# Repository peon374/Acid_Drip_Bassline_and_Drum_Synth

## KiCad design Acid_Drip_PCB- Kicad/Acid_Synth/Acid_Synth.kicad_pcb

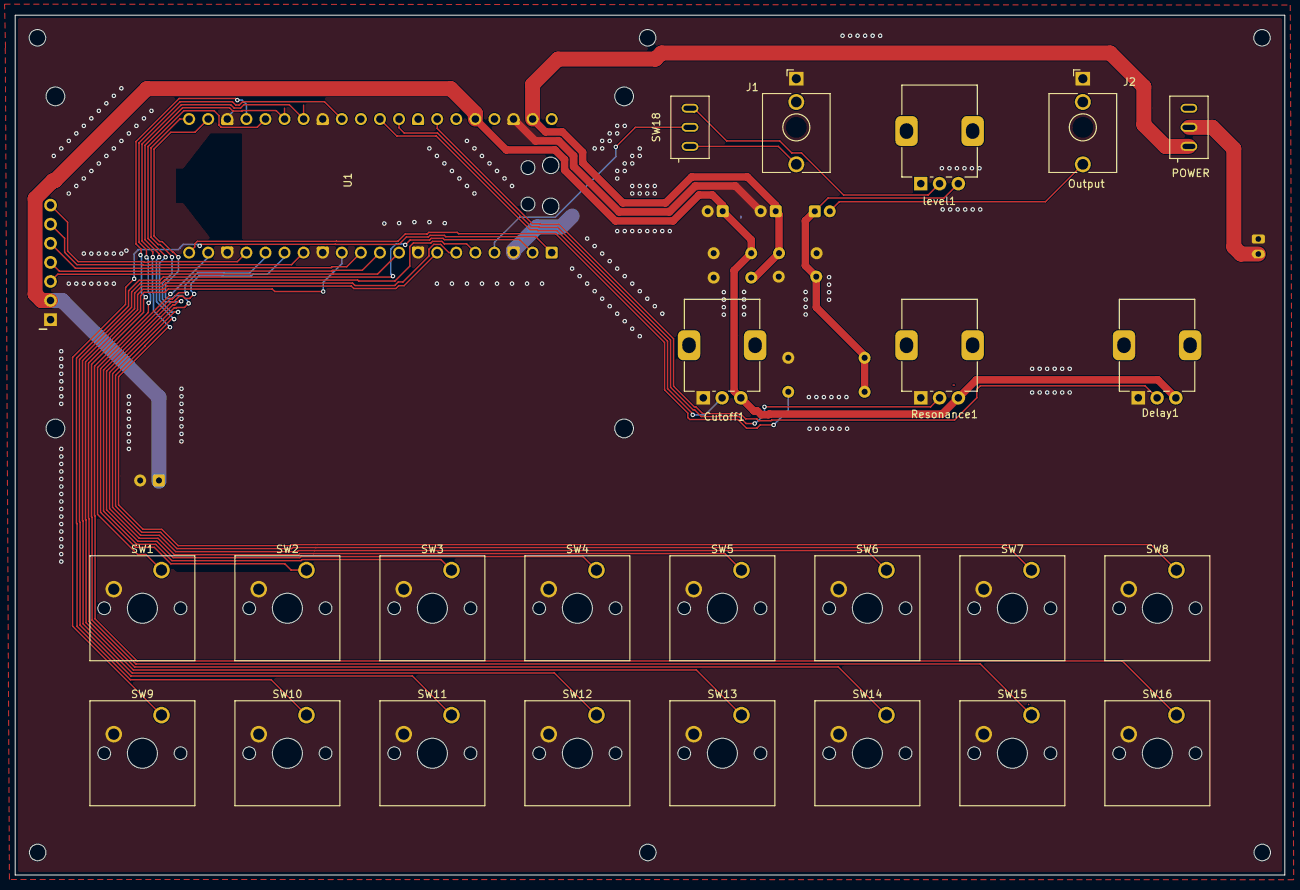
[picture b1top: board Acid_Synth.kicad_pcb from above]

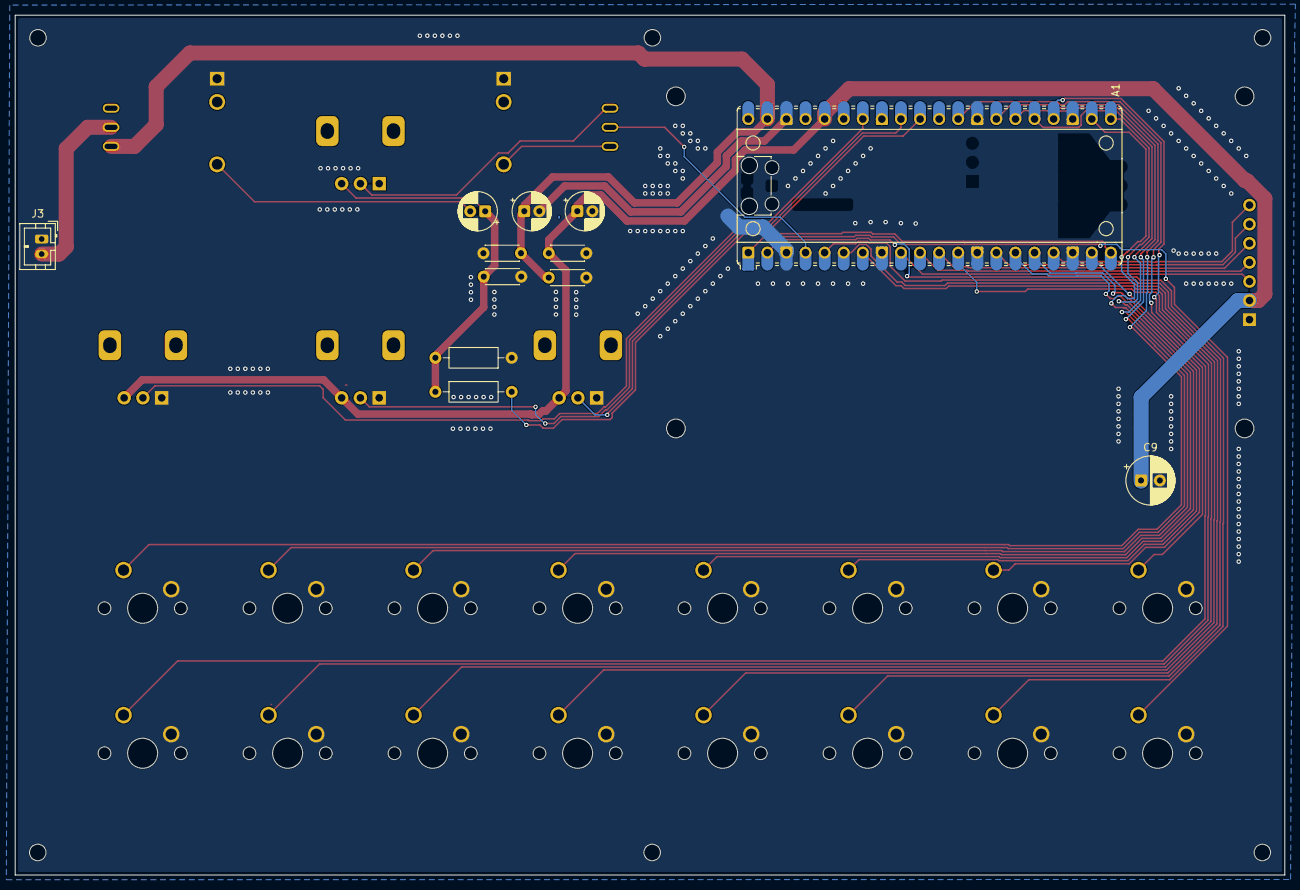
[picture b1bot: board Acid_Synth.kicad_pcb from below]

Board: 2 copper layers, 169.0 x 114.4 mm, 37 parts (12 on the bottom side), 33 nets.

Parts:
A1: RaspberryPi_Pico; RaspberryPi_Pico_Common
C1, C2, C4: 100nf; C_Disc_D4.3mm_W1.9mm_P5.00mm
C3, C5, C6: 100uf; CP_Radial_D5.0mm_P2.00mm
C7: 10nf; C_Disc_D4.3mm_W1.9mm_P5.00mm
C9: 1000uf; CP_Radial_D6.3mm_P2.50mm
Cutoff1: 10K; Potentiometer_Alps_RK09K_Single_Vertical
Delay1: 10K; Potentiometer_Alps_RK09K_Single_Vertical
J1: Sync_In; Jack_3.5mm_QingPu_WQP-PJ398SM_Vertical_CircularHoles
J2: Output; Jack_3.5mm_QingPu_WQP-PJ398SM_Vertical_CircularHoles
J3: Conn_01x02_Socket; JST_PH_B2B-PH-K_1x02_P2.00mm_Vertical
R1: 3.3K; R_Axial_DIN0207_L6.3mm_D2.5mm_P10.16mm_Horizontal
R3: 10K; R_Axial_DIN0207_L6.3mm_D2.5mm_P10.16mm_Horizontal
Resonance1: 10K; Potentiometer_Alps_RK09K_Single_Vertical
SW1, SW2, SW3, SW4, SW5, SW6, SW7, SW8, SW9, SW10, SW11, SW12, SW13, SW14, SW15, SW16: SW_Cherry_MX_1.00u_PCB
SW17: POWER; SW_SPDT_Toggle_QuarterInch_Bushing
SW18: SW_SPDT; SW_SPDT_Toggle_QuarterInch_Bushing
U1: TFT_2.8in_ILI9341
level1: 50K; Potentiometer_Alps_RK09K_Single_Vertical

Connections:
+3.3V: A1.36 (3V3), C2.1, C3.1, C9.1, Cutoff1.3, Delay1.3, Resonance1.3, U1.2 (VCC)
+5V: A1.39 (VSYS), C1.1, C4.1, C5.1, SW17.1 (A)
+BATT: J3.2, SW17.2 (B)
CS: A1.17 (GPIO13), U1.7 (CS)
Cutoff: A1.31 (GPIO26_ADC0), Cutoff1.2
DC: A1.14 (GPIO10), U1.6 (DC)
Decay: A1.34 (GPIO28_ADC2), Delay1.2
GND: A1.3 (GND), A1.8 (GND), A1.13 (GND), A1.18 (GND), A1.23 (GND), A1.28 (GND), A1.38 (GND), C1.2, C2.2, C3.2, C4.2, C5.2, C7.1, C9.2, Cutoff1.1, Delay1.1, J1.S, J2.S, J3.1, R1.1, Resonance1.1, SW1.2, SW2.2, SW3.2, SW4.2, SW5.2, SW6.2, SW7.2, SW8.2, SW9.2, SW10.2, SW11.2, SW12.2, SW13.2, SW14.2, SW15.2, SW16.2, U1.1 (GND)
NODE: C6.1, C7.2, R1.2, R3.1, level1.3
unnamed: C6.2, J2.T
unnamed: J1.T, SW18.1 (A)
OUTPUT: A1.20 (GPIO15), R3.2
RST: A1.11 (GPIO8), U1.5 (RST)
Resonance: A1.32 (GPIO27_ADC1), Resonance1.2
SCL: A1.9 (GPIO6), U1.3 (SCL)
SDA: A1.10 (GPIO7), U1.4 (SDA)
SW1: A1.19 (GPIO14), SW1.1
SW2: A1.16 (GPIO12), SW2.1
SW3: A1.15 (GPIO11), SW3.1
SW4: A1.21 (GPIO16), SW4.1
SW5: A1.22 (GPIO17), SW5.1
SW6: A1.25 (GPIO19), SW6.1
SW7: A1.26 (GPIO20), SW7.1
SW8: A1.27 (GPIO21), SW8.1
SW9: A1.1 (GPIO0), SW9.1
SW10: A1.2 (GPIO1), SW10.1
SW11: A1.5 (GPIO3), SW11.1
SW12: A1.6 (GPIO4), SW12.1
SW13: A1.7 (GPIO5), SW13.1
SW14: A1.12 (GPIO9), SW14.1
SW15: A1.24 (GPIO18), SW15.1
SYNC_IN: A1.4 (GPIO2), SW18.2 (B)
W16: A1.29 (GPIO22), SW16.1
